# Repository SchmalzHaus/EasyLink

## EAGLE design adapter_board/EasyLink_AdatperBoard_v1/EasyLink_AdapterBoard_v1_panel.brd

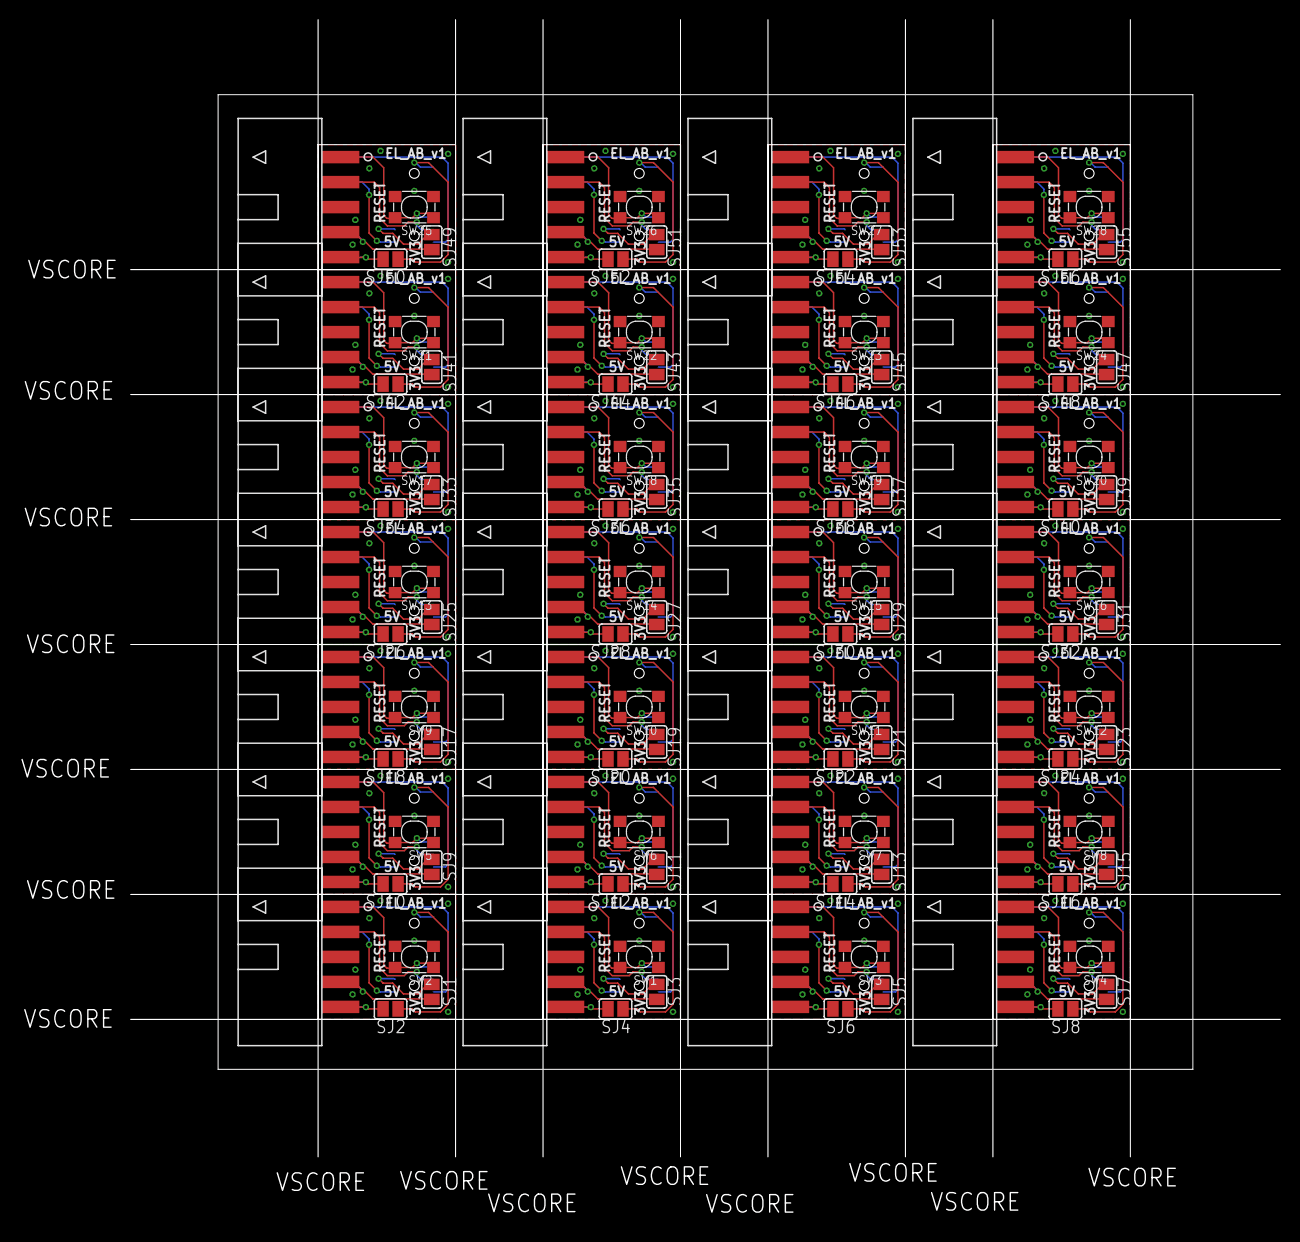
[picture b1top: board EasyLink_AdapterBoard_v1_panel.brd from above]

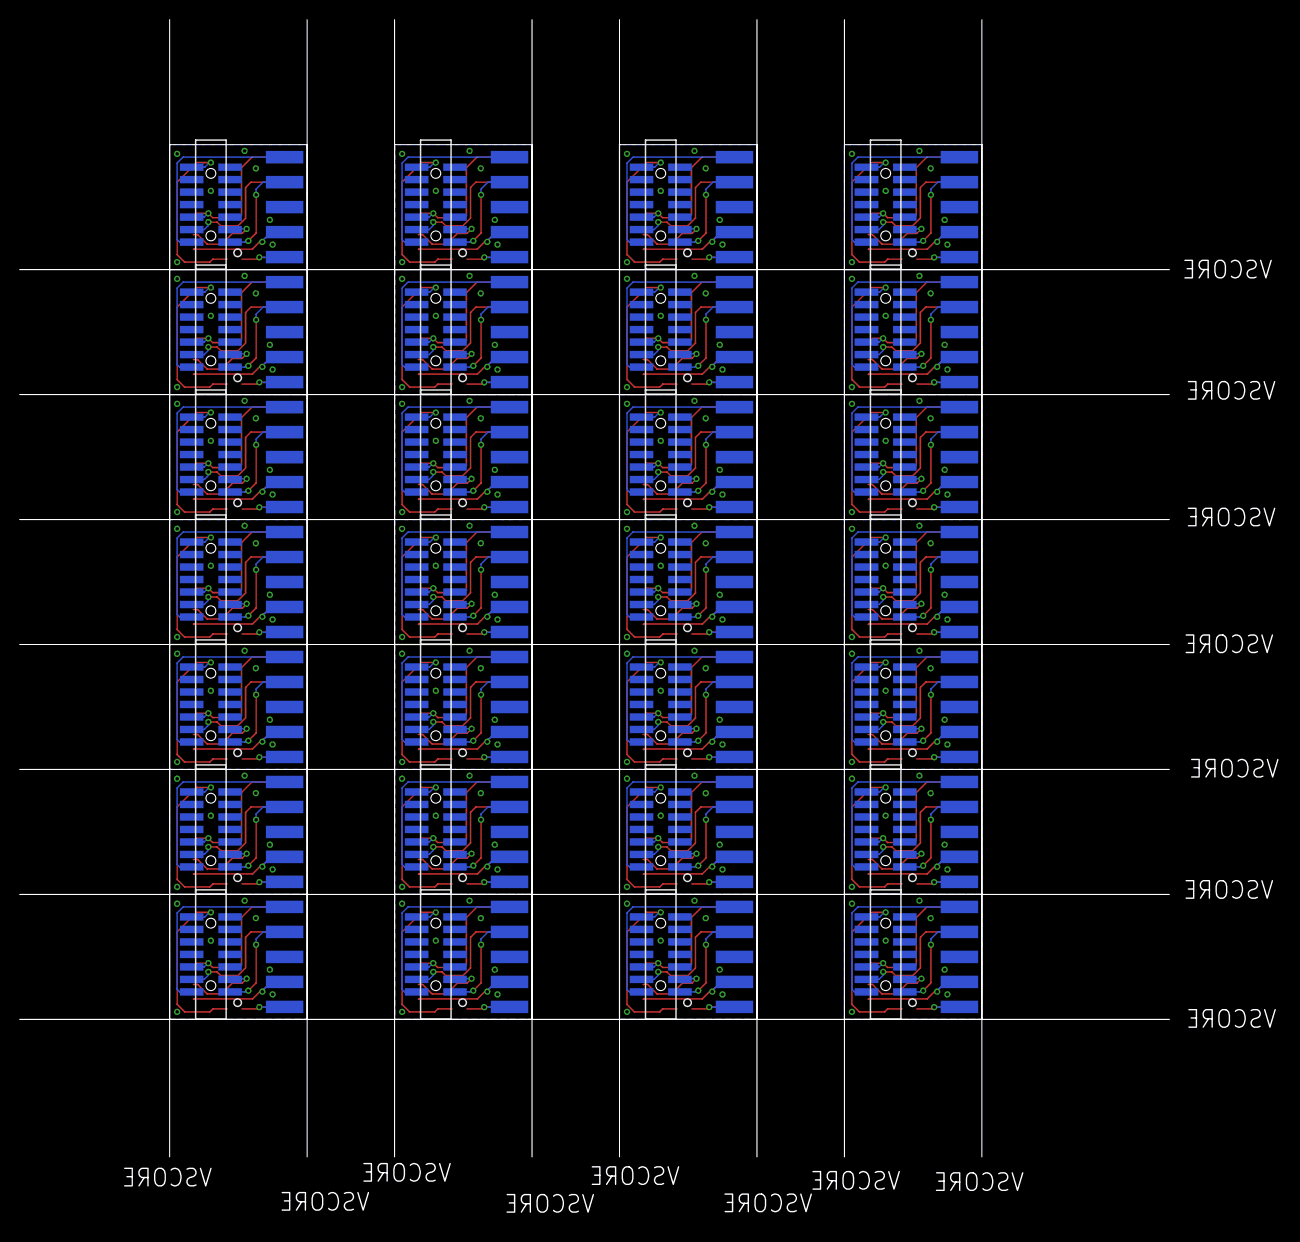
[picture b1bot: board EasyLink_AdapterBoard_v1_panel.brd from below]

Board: 4 copper layers, 116.8 x 115.6 mm, 140 parts (28 on the bottom side), 252 nets.

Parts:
SJ1, SJ2, SJ3, SJ4, SJ5, SJ6, SJ7, SJ8, SJ9, SJ10, SJ11, SJ12, SJ13, SJ14, SJ15, SJ16, SJ17, SJ18, SJ19, SJ20, SJ21, SJ22, SJ23, SJ24, SJ25, SJ26, SJ27, SJ28, SJ29, SJ30, SJ31, SJ32, SJ33, SJ34, SJ35, SJ36, SJ37, SJ38, SJ39, SJ40, SJ41, SJ42, SJ43, SJ44, SJ45, SJ46, SJ47, SJ48, SJ49, SJ50, SJ51, SJ52, SJ53, SJ54, SJ55, SJ56: SJ
SW1, SW2, SW3, SW4, SW5, SW6, SW7, SW8, SW9, SW10, SW11, SW12, SW13, SW14, SW15, SW16, SW17, SW18, SW19, SW20, SW21, SW22, SW23, SW24, SW25, SW26, SW27, SW28: DHT-4235A; SW4-SMD-4.2X3.2X2.5MM
U$1, U$3, U$5, U$7, U$9, U$11, U$13, U$15, U$17, U$19, U$21, U$23, U$25, U$27, U$29, U$31, U$33, U$35, U$37, U$39, U$41, U$43, U$45, U$47, U$49, U$51, U$53, U$55: 2X7_DEBUG_HEADFER; 20021121_2X7_SMT_MALE
U$2, U$4, U$6, U$8, U$10, U$12, U$14, U$16, U$18, U$20, U$22, U$24, U$26, U$28, U$30, U$32, U$34, U$36, U$38, U$40, U$42, U$44, U$46, U$48, U$50, U$52, U$54, U$56: SFH11-2X5STRAIGHT; SFH11-2X5-STRAIGHT

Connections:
GND: SW2.3, SW2.4, U$1.P$5, U$1.P$7, U$1.P$8, U$2.P5, U$2.P6
GND1: SW1.3, SW1.4, U$3.P$5, U$3.P$7, U$3.P$8, U$4.P5, U$4.P6
GND2: SW3.3, SW3.4, U$5.P$5, U$5.P$7, U$5.P$8, U$6.P5, U$6.P6
GND3: SW4.3, SW4.4, U$7.P$5, U$7.P$7, U$7.P$8, U$8.P5, U$8.P6
GND4: SW5.3, SW5.4, U$9.P$5, U$9.P$7, U$9.P$8, U$10.P5, U$10.P6
GND5: SW6.3, SW6.4, U$11.P$5, U$11.P$7, U$11.P$8, U$12.P5, U$12.P6
GND6: SW7.3, SW7.4, U$13.P$5, U$13.P$7, U$13.P$8, U$14.P5, U$14.P6
GND7: SW8.3, SW8.4, U$15.P$5, U$15.P$7, U$15.P$8, U$16.P5, U$16.P6
GND8: SW9.3, SW9.4, U$17.P$5, U$17.P$7, U$17.P$8, U$18.P5, U$18.P6
GND9: SW10.3, SW10.4, U$19.P$5, U$19.P$7, U$19.P$8, U$20.P5, U$20.P6
GND10: SW11.3, SW11.4, U$21.P$5, U$21.P$7, U$21.P$8, U$22.P5, U$22.P6
GND11: SW12.3, SW12.4, U$23.P$5, U$23.P$7, U$23.P$8, U$24.P5, U$24.P6
GND12: SW13.3, SW13.4, U$25.P$5, U$25.P$7, U$25.P$8, U$26.P5, U$26.P6
GND13: SW14.3, SW14.4, U$27.P$5, U$27.P$7, U$27.P$8, U$28.P5, U$28.P6
GND14: SW15.3, SW15.4, U$29.P$5, U$29.P$7, U$29.P$8, U$30.P5, U$30.P6
GND15: SW16.3, SW16.4, U$31.P$5, U$31.P$7, U$31.P$8, U$32.P5, U$32.P6
GND16: SW17.3, SW17.4, U$33.P$5, U$33.P$7, U$33.P$8, U$34.P5, U$34.P6
GND17: SW18.3, SW18.4, U$35.P$5, U$35.P$7, U$35.P$8, U$36.P5, U$36.P6
GND18: SW19.3, SW19.4, U$37.P$5, U$37.P$7, U$37.P$8, U$38.P5, U$38.P6
GND19: SW20.3, SW20.4, U$39.P$5, U$39.P$7, U$39.P$8, U$40.P5, U$40.P6
GND20: SW21.3, SW21.4, U$41.P$5, U$41.P$7, U$41.P$8, U$42.P5, U$42.P6
GND21: SW22.3, SW22.4, U$43.P$5, U$43.P$7, U$43.P$8, U$44.P5, U$44.P6
GND22: SW23.3, SW23.4, U$45.P$5, U$45.P$7, U$45.P$8, U$46.P5, U$46.P6
GND23: SW24.3, SW24.4, U$47.P$5, U$47.P$7, U$47.P$8, U$48.P5, U$48.P6
GND24: SW25.3, SW25.4, U$49.P$5, U$49.P$7, U$49.P$8, U$50.P5, U$50.P6
GND25: SW26.3, SW26.4, U$51.P$5, U$51.P$7, U$51.P$8, U$52.P5, U$52.P6
GND26: SW27.3, SW27.4, U$53.P$5, U$53.P$7, U$53.P$8, U$54.P5, U$54.P6
GND27: SW28.3, SW28.4, U$55.P$5, U$55.P$7, U$55.P$8, U$56.P5, U$56.P6
unnamed: U$1.P$1, U$2.P4
unnamed: U$1.P$2, U$2.P2
unnamed: SJ1.2, U$2.P7, U$2.P8
unnamed: U$1.P$4, U$2.P3
unnamed: SJ2.1, U$1.P$14
unnamed: U$3.P$1, U$4.P4
unnamed: SJ2.2, U$2.P9, U$2.P10
unnamed: SJ1.1, U$1.P$3
unnamed: U$3.P$2, U$4.P2
unnamed: SJ3.2, U$4.P7, U$4.P8
unnamed: U$3.P$4, U$4.P3
unnamed: SJ4.2, U$4.P9, U$4.P10
unnamed: SJ4.1, U$3.P$14
unnamed: SJ3.1, U$3.P$3
unnamed: U$5.P$1, U$6.P4
unnamed: U$5.P$2, U$6.P2
unnamed: SJ5.2, U$6.P7, U$6.P8
unnamed: U$5.P$4, U$6.P3
unnamed: SJ6.2, U$6.P9, U$6.P10
unnamed: SJ6.1, U$5.P$14
unnamed: SJ5.1, U$5.P$3
unnamed: U$7.P$1, U$8.P4
unnamed: U$7.P$2, U$8.P2
unnamed: SJ7.2, U$8.P7, U$8.P8
unnamed: U$7.P$4, U$8.P3
unnamed: SJ8.2, U$8.P9, U$8.P10
unnamed: SJ8.1, U$7.P$14
unnamed: SJ7.1, U$7.P$3
unnamed: U$9.P$1, U$10.P4
unnamed: U$9.P$2, U$10.P2
unnamed: SJ9.2, U$10.P7, U$10.P8
unnamed: U$9.P$4, U$10.P3
unnamed: SJ10.2, U$10.P9, U$10.P10
unnamed: SJ10.1, U$9.P$14
unnamed: SJ9.1, U$9.P$3
unnamed: U$11.P$1, U$12.P4
unnamed: U$11.P$2, U$12.P2
unnamed: SJ11.2, U$12.P7, U$12.P8
unnamed: U$11.P$4, U$12.P3
unnamed: SJ12.2, U$12.P9, U$12.P10
unnamed: SJ12.1, U$11.P$14
unnamed: SJ11.1, U$11.P$3
unnamed: U$13.P$1, U$14.P4
unnamed: U$13.P$2, U$14.P2
unnamed: SJ13.2, U$14.P7, U$14.P8
unnamed: U$13.P$4, U$14.P3
unnamed: SJ14.2, U$14.P9, U$14.P10
unnamed: SJ14.1, U$13.P$14
unnamed: SJ13.1, U$13.P$3
unnamed: U$15.P$1, U$16.P4
unnamed: U$15.P$2, U$16.P2
unnamed: SJ15.2, U$16.P7, U$16.P8
unnamed: U$15.P$4, U$16.P3
unnamed: SJ16.2, U$16.P9, U$16.P10
unnamed: SJ16.1, U$15.P$14
unnamed: SJ15.1, U$15.P$3
unnamed: U$17.P$1, U$18.P4
unnamed: U$17.P$2, U$18.P2
unnamed: SJ17.2, U$18.P7, U$18.P8
unnamed: U$17.P$4, U$18.P3
unnamed: SJ18.2, U$18.P9, U$18.P10
unnamed: SJ18.1, U$17.P$14
unnamed: SJ17.1, U$17.P$3
unnamed: U$19.P$1, U$20.P4
unnamed: U$19.P$2, U$20.P2
unnamed: SJ19.2, U$20.P7, U$20.P8
unnamed: U$19.P$4, U$20.P3
unnamed: SJ20.2, U$20.P9, U$20.P10
unnamed: SJ20.1, U$19.P$14
unnamed: SJ19.1, U$19.P$3
unnamed: U$21.P$1, U$22.P4
unnamed: U$21.P$2, U$22.P2
unnamed: SJ21.2, U$22.P7, U$22.P8
unnamed: U$21.P$4, U$22.P3
unnamed: SJ22.2, U$22.P9, U$22.P10
unnamed: SJ22.1, U$21.P$14
unnamed: SJ21.1, U$21.P$3
unnamed: U$23.P$1, U$24.P4
unnamed: U$23.P$2, U$24.P2
unnamed: SJ23.2, U$24.P7, U$24.P8
unnamed: U$23.P$4, U$24.P3
unnamed: SJ24.2, U$24.P9, U$24.P10
unnamed: SJ24.1, U$23.P$14
unnamed: SJ23.1, U$23.P$3
unnamed: U$25.P$1, U$26.P4
unnamed: U$25.P$2, U$26.P2
unnamed: SJ25.2, U$26.P7, U$26.P8
unnamed: U$25.P$4, U$26.P3
unnamed: SJ26.2, U$26.P9, U$26.P10
unnamed: SJ26.1, U$25.P$14
unnamed: SJ25.1, U$25.P$3
unnamed: U$27.P$1, U$28.P4
unnamed: U$27.P$2, U$28.P2
unnamed: SJ27.2, U$28.P7, U$28.P8
unnamed: U$27.P$4, U$28.P3
unnamed: SJ28.2, U$28.P9, U$28.P10
unnamed: SJ28.1, U$27.P$14
unnamed: SJ27.1, U$27.P$3
unnamed: U$29.P$1, U$30.P4
unnamed: U$29.P$2, U$30.P2
unnamed: SJ29.2, U$30.P7, U$30.P8
unnamed: U$29.P$4, U$30.P3
unnamed: SJ30.2, U$30.P9, U$30.P10
unnamed: SJ30.1, U$29.P$14
unnamed: SJ29.1, U$29.P$3
unnamed: U$31.P$1, U$32.P4
unnamed: U$31.P$2, U$32.P2
unnamed: SJ31.2, U$32.P7, U$32.P8
unnamed: U$31.P$4, U$32.P3
unnamed: SJ32.2, U$32.P9, U$32.P10
unnamed: SJ32.1, U$31.P$14
unnamed: SJ31.1, U$31.P$3
unnamed: U$33.P$1, U$34.P4
unnamed: U$33.P$2, U$34.P2
unnamed: SJ33.2, U$34.P7, U$34.P8
unnamed: U$33.P$4, U$34.P3
unnamed: SJ34.2, U$34.P9, U$34.P10
unnamed: SJ34.1, U$33.P$14
unnamed: SJ33.1, U$33.P$3
unnamed: U$35.P$1, U$36.P4
unnamed: U$35.P$2, U$36.P2
unnamed: SJ35.2, U$36.P7, U$36.P8
unnamed: U$35.P$4, U$36.P3
unnamed: SJ36.2, U$36.P9, U$36.P10
unnamed: SJ36.1, U$35.P$14
unnamed: SJ35.1, U$35.P$3
unnamed: U$37.P$1, U$38.P4
unnamed: U$37.P$2, U$38.P2
unnamed: SJ37.2, U$38.P7, U$38.P8
unnamed: U$37.P$4, U$38.P3
unnamed: SJ38.2, U$38.P9, U$38.P10
unnamed: SJ38.1, U$37.P$14
unnamed: SJ37.1, U$37.P$3
unnamed: U$39.P$1, U$40.P4
unnamed: U$39.P$2, U$40.P2
unnamed: SJ39.2, U$40.P7, U$40.P8
unnamed: U$39.P$4, U$40.P3
unnamed: SJ40.2, U$40.P9, U$40.P10
unnamed: SJ40.1, U$39.P$14
unnamed: SJ39.1, U$39.P$3
unnamed: U$41.P$1, U$42.P4
unnamed: U$41.P$2, U$42.P2
unnamed: SJ41.2, U$42.P7, U$42.P8
unnamed: U$41.P$4, U$42.P3
unnamed: SJ42.2, U$42.P9, U$42.P10
unnamed: SJ42.1, U$41.P$14
unnamed: SJ41.1, U$41.P$3
unnamed: U$43.P$1, U$44.P4
unnamed: U$43.P$2, U$44.P2
unnamed: SJ43.2, U$44.P7, U$44.P8
unnamed: U$43.P$4, U$44.P3
unnamed: SJ44.2, U$44.P9, U$44.P10
unnamed: SJ44.1, U$43.P$14
unnamed: SJ43.1, U$43.P$3
unnamed: U$45.P$1, U$46.P4
unnamed: U$45.P$2, U$46.P2
unnamed: SJ45.2, U$46.P7, U$46.P8
unnamed: U$45.P$4, U$46.P3
unnamed: SJ46.2, U$46.P9, U$46.P10
unnamed: SJ46.1, U$45.P$14
unnamed: SJ45.1, U$45.P$3
unnamed: U$47.P$1, U$48.P4
unnamed: U$47.P$2, U$48.P2
unnamed: SJ47.2, U$48.P7, U$48.P8
unnamed: U$47.P$4, U$48.P3
unnamed: SJ48.2, U$48.P9, U$48.P10
unnamed: SJ48.1, U$47.P$14
unnamed: SJ47.1, U$47.P$3
unnamed: U$49.P$1, U$50.P4
unnamed: U$49.P$2, U$50.P2
unnamed: SJ49.2, U$50.P7, U$50.P8
unnamed: U$49.P$4, U$50.P3
unnamed: SJ50.2, U$50.P9, U$50.P10
unnamed: SJ50.1, U$49.P$14
unnamed: SJ49.1, U$49.P$3
unnamed: U$51.P$1, U$52.P4
unnamed: U$51.P$2, U$52.P2
unnamed: SJ51.2, U$52.P7, U$52.P8
unnamed: U$51.P$4, U$52.P3
unnamed: SJ52.2, U$52.P9, U$52.P10
unnamed: SJ52.1, U$51.P$14
unnamed: SJ51.1, U$51.P$3
unnamed: U$53.P$1, U$54.P4
unnamed: U$53.P$2, U$54.P2
unnamed: SJ53.2, U$54.P7, U$54.P8
unnamed: U$53.P$4, U$54.P3
unnamed: SJ54.2, U$54.P9, U$54.P10
unnamed: SJ54.1, U$53.P$14
unnamed: SJ53.1, U$53.P$3
unnamed: U$55.P$1, U$56.P4
unnamed: U$55.P$2, U$56.P2
unnamed: SJ55.2, U$56.P7, U$56.P8
unnamed: U$55.P$4, U$56.P3
unnamed: SJ56.2, U$56.P9, U$56.P10
unnamed: SJ56.1, U$55.P$14
unnamed: SJ55.1, U$55.P$3
PRG_SW: SW2.1, SW2.2, U$1.P$6, U$2.P1
PRG_SW1: SW1.1, SW1.2, U$3.P$6, U$4.P1
PRG_SW2: SW3.1, SW3.2, U$5.P$6, U$6.P1
PRG_SW3: SW4.1, SW4.2, U$7.P$6, U$8.P1
PRG_SW4: SW5.1, SW5.2, U$9.P$6, U$10.P1
PRG_SW5: SW6.1, SW6.2, U$11.P$6, U$12.P1
PRG_SW6: SW7.1, SW7.2, U$13.P$6, U$14.P1
PRG_SW7: SW8.1, SW8.2, U$15.P$6, U$16.P1
PRG_SW8: SW9.1, SW9.2, U$17.P$6, U$18.P1
PRG_SW9: SW10.1, SW10.2, U$19.P$6, U$20.P1
PRG_SW10: SW11.1, SW11.2, U$21.P$6, U$22.P1
PRG_SW11: SW12.1, SW12.2, U$23.P$6, U$24.P1
PRG_SW12: SW13.1, SW13.2, U$25.P$6, U$26.P1
PRG_SW13: SW14.1, SW14.2, U$27.P$6, U$28.P1
PRG_SW14: SW15.1, SW15.2, U$29.P$6, U$30.P1
PRG_SW15: SW16.1, SW16.2, U$31.P$6, U$32.P1
PRG_SW16: SW17.1, SW17.2, U$33.P$6, U$34.P1
PRG_SW17: SW18.1, SW18.2, U$35.P$6, U$36.P1
PRG_SW18: SW19.1, SW19.2, U$37.P$6, U$38.P1
PRG_SW19: SW20.1, SW20.2, U$39.P$6, U$40.P1
PRG_SW20: SW21.1, SW21.2, U$41.P$6, U$42.P1
PRG_SW21: SW22.1, SW22.2, U$43.P$6, U$44.P1
PRG_SW22: SW23.1, SW23.2, U$45.P$6, U$46.P1
PRG_SW23: SW24.1, SW24.2, U$47.P$6, U$48.P1
PRG_SW24: SW25.1, SW25.2, U$49.P$6, U$50.P1
PRG_SW25: SW26.1, SW26.2, U$51.P$6, U$52.P1
PRG_SW26: SW27.1, SW27.2, U$53.P$6, U$54.P1
PRG_SW27: SW28.1, SW28.2, U$55.P$6, U$56.P1

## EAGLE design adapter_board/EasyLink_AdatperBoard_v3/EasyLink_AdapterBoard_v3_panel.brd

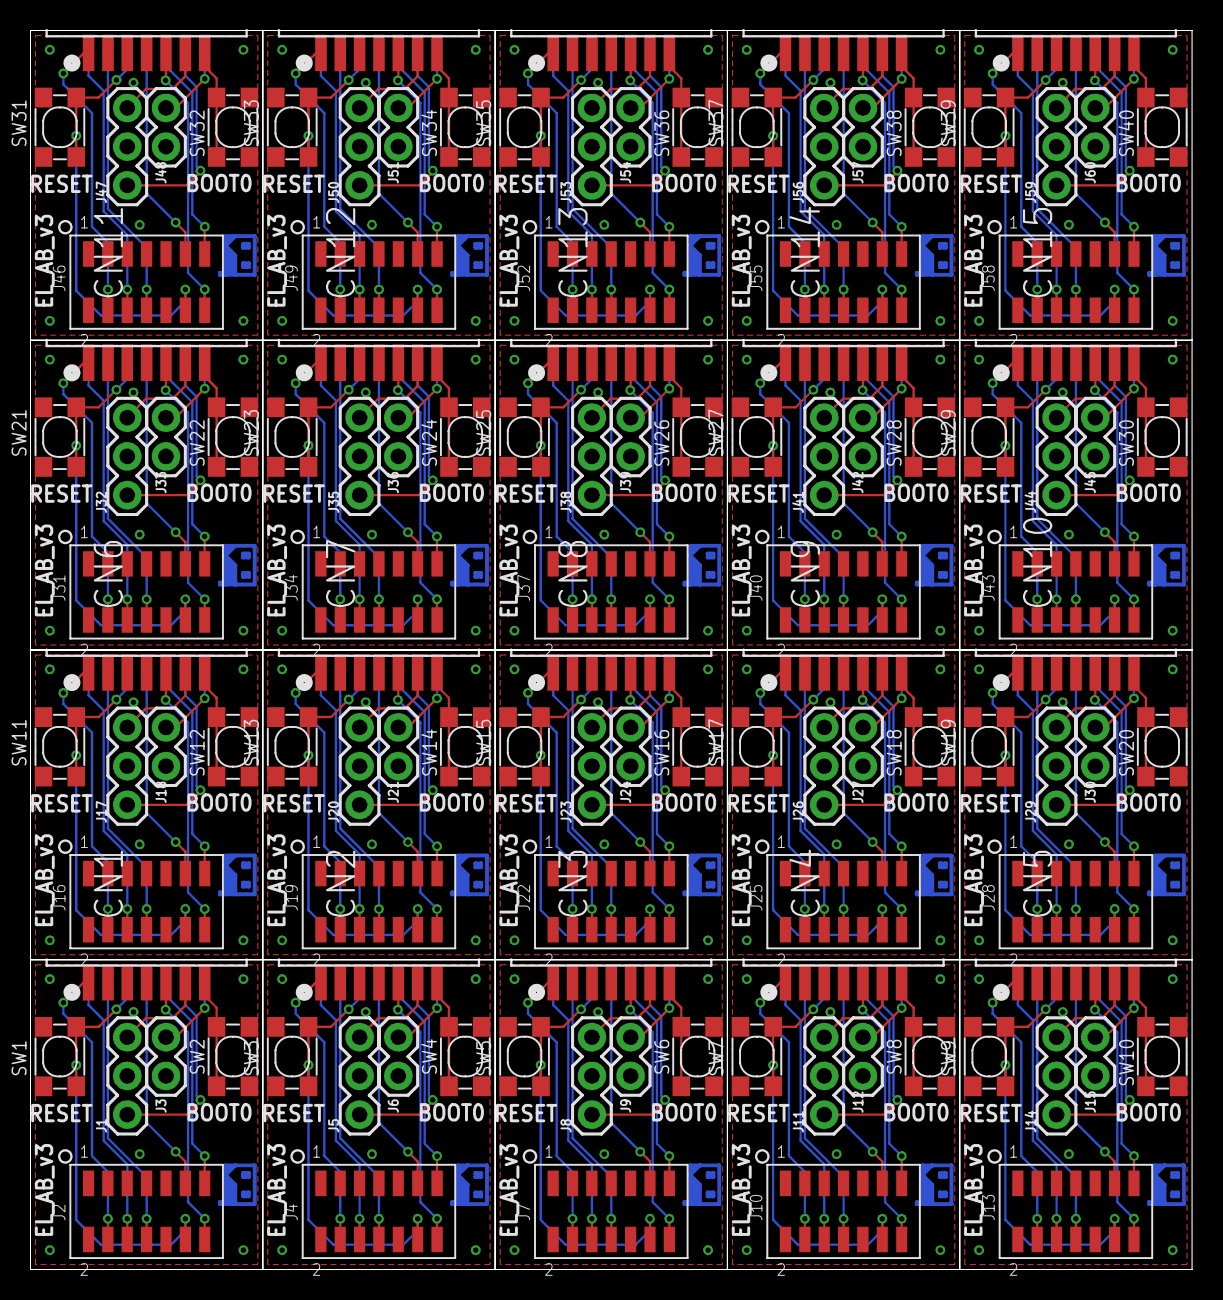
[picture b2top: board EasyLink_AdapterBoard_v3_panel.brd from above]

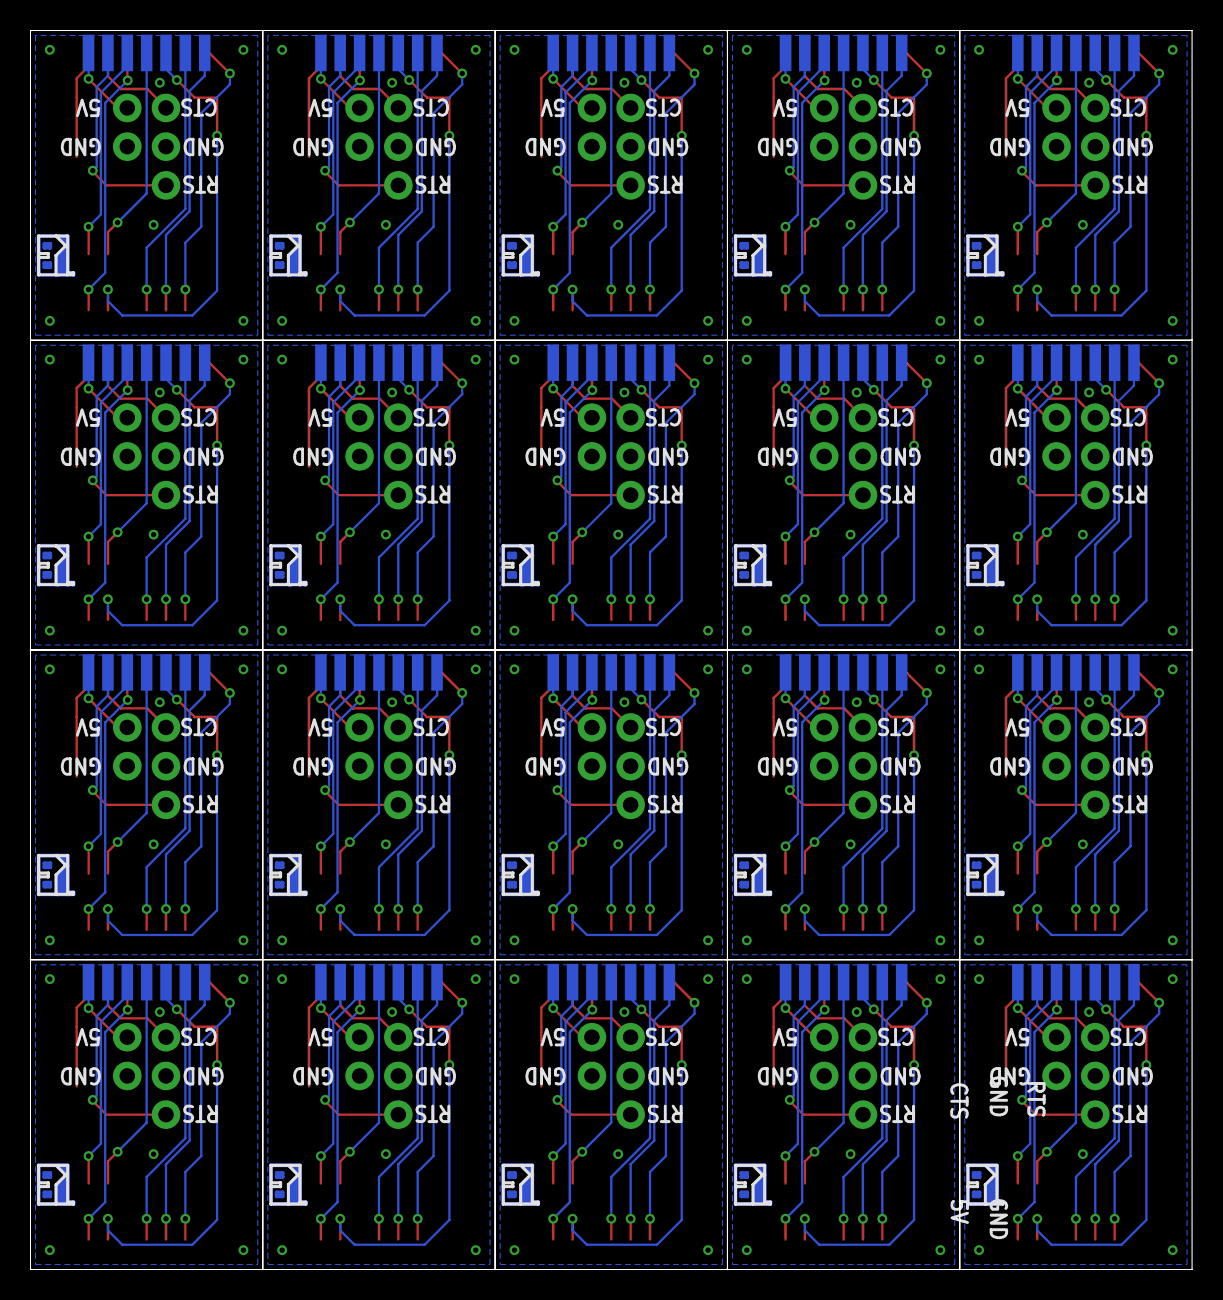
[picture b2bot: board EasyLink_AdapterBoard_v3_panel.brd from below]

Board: 2 copper layers, 76.2 x 81.3 mm, 140 parts (20 on the bottom side), 240 nets.

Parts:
CN1, CN2, CN3, CN4, CN5, CN6, CN7, CN8, CN9, CN10, CN11, CN12, CN13, CN14, CN15, CN16, CN17, CN18, CN19, CN20: 2X7_DEBUG_HEADFEREDGE; 2X7_MALE_BOARD_STRADDLE
J1, J5, J8, J11, J14, J17, J20, J23, J26, J29, J32, J35, J38, J41, J44, J47, J50, J53, J56, J59: 1X03
J2, J4, J7, J10, J13, J16, J19, J22, J25, J28, J31, J34, J37, J40, J43, J46, J49, J52, J55, J58: FLE-107-01-XX-DV
J3, J6, J9, J12, J15, J18, J21, J24, J27, J30, J33, J36, J39, J42, J45, J48, J51, J54, J57, J60: 1X02
SW1, SW2, SW3, SW4, SW5, SW6, SW7, SW8, SW9, SW10, SW11, SW12, SW13, SW14, SW15, SW16, SW17, SW18, SW19, SW20, SW21, SW22, SW23, SW24, SW25, SW26, SW27, SW28, SW29, SW30, SW31, SW32, SW33, SW34, SW35, SW36, SW37, SW38, SW39, SW40: DHT-4235A; SW4-SMD-4.2X3.2X2.5MM
U$1, U$2, U$3, U$4, U$5, U$6, U$7, U$8, U$9, U$10, U$11, U$12, U$13, U$14, U$15, U$16, U$17, U$18, U$19, U$20: SCHMALZHAUSSCHMALZHAUS_SMALL; SCHMALZHAUS_SMALL

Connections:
5V: CN1.P$14, J3.1
5V1: CN2.P$14, J6.1
5V2: CN3.P$14, J9.1
5V3: CN4.P$14, J12.1
5V4: CN5.P$14, J15.1
5V5: CN6.P$14, J18.1
5V6: CN7.P$14, J21.1
5V7: CN8.P$14, J24.1
5V8: CN9.P$14, J27.1
5V9: CN10.P$14, J30.1
5V10: CN11.P$14, J33.1
5V11: CN12.P$14, J36.1
5V12: CN13.P$14, J39.1
5V13: CN14.P$14, J42.1
5V14: CN15.P$14, J45.1
5V15: CN16.P$14, J48.1
5V16: CN17.P$14, J51.1
5V17: CN18.P$14, J54.1
5V18: CN19.P$14, J57.1
5V19: CN20.P$14, J60.1
BOOT0: CN1.P$13, SW2.1, SW2.2
BOOT1: CN2.P$13, SW4.1, SW4.2
BOOT2: CN3.P$13, SW6.1, SW6.2
BOOT3: CN4.P$13, SW8.1, SW8.2
BOOT4: CN5.P$13, SW10.1, SW10.2
BOOT5: CN6.P$13, SW12.1, SW12.2
BOOT6: CN7.P$13, SW14.1, SW14.2
BOOT7: CN8.P$13, SW16.1, SW16.2
BOOT8: CN9.P$13, SW18.1, SW18.2
BOOT9: CN10.P$13, SW20.1, SW20.2
BOOT10: CN11.P$13, SW22.1, SW22.2
BOOT11: CN12.P$13, SW24.1, SW24.2
BOOT12: CN13.P$13, SW26.1, SW26.2
BOOT13: CN14.P$13, SW28.1, SW28.2
BOOT14: CN15.P$13, SW30.1, SW30.2
BOOT15: CN16.P$13, SW32.1, SW32.2
BOOT16: CN17.P$13, SW34.1, SW34.2
BOOT17: CN18.P$13, SW36.1, SW36.2
BOOT18: CN19.P$13, SW38.1, SW38.2
BOOT19: CN20.P$13, SW40.1, SW40.2
CTS: CN1.P$11, J1.3
CTS1: CN2.P$11, J5.3
CTS2: CN3.P$11, J8.3
CTS3: CN4.P$11, J11.3
CTS4: CN5.P$11, J14.3
CTS5: CN6.P$11, J17.3
CTS6: CN7.P$11, J20.3
CTS7: CN8.P$11, J23.3
CTS8: CN9.P$11, J26.3
CTS9: CN10.P$11, J29.3
CTS10: CN11.P$11, J32.3
CTS11: CN12.P$11, J35.3
CTS12: CN13.P$11, J38.3
CTS13: CN14.P$11, J41.3
CTS14: CN15.P$11, J44.3
CTS15: CN16.P$11, J47.3
CTS16: CN17.P$11, J50.3
CTS17: CN18.P$11, J53.3
CTS18: CN19.P$11, J56.3
CTS19: CN20.P$11, J59.3
GND: CN1.P$5, CN1.P$7, J1.2, J2.5, J2.7, J3.2, SW1.3, SW1.4, SW2.3, SW2.4
GND1: CN2.P$5, CN2.P$7, J4.5, J4.7, J5.2, J6.2, SW3.3, SW3.4, SW4.3, SW4.4
GND2: CN3.P$5, CN3.P$7, J7.5, J7.7, J8.2, J9.2, SW5.3, SW5.4, SW6.3, SW6.4
GND3: CN4.P$5, CN4.P$7, J10.5, J10.7, J11.2, J12.2, SW7.3, SW7.4, SW8.3, SW8.4
GND4: CN5.P$5, CN5.P$7, J13.5, J13.7, J14.2, J15.2, SW9.3, SW9.4, SW10.3, SW10.4
GND5: CN6.P$5, CN6.P$7, J16.5, J16.7, J17.2, J18.2, SW11.3, SW11.4, SW12.3, SW12.4
GND6: CN7.P$5, CN7.P$7, J19.5, J19.7, J20.2, J21.2, SW13.3, SW13.4, SW14.3, SW14.4
GND7: CN8.P$5, CN8.P$7, J22.5, J22.7, J23.2, J24.2, SW15.3, SW15.4, SW16.3, SW16.4
GND8: CN9.P$5, CN9.P$7, J25.5, J25.7, J26.2, J27.2, SW17.3, SW17.4, SW18.3, SW18.4
GND9: CN10.P$5, CN10.P$7, J28.5, J28.7, J29.2, J30.2, SW19.3, SW19.4, SW20.3, SW20.4
GND10: CN11.P$5, CN11.P$7, J31.5, J31.7, J32.2, J33.2, SW21.3, SW21.4, SW22.3, SW22.4
GND11: CN12.P$5, CN12.P$7, J34.5, J34.7, J35.2, J36.2, SW23.3, SW23.4, SW24.3, SW24.4
GND12: CN13.P$5, CN13.P$7, J37.5, J37.7, J38.2, J39.2, SW25.3, SW25.4, SW26.3, SW26.4
GND13: CN14.P$5, CN14.P$7, J40.5, J40.7, J41.2, J42.2, SW27.3, SW27.4, SW28.3, SW28.4
GND14: CN15.P$5, CN15.P$7, J43.5, J43.7, J44.2, J45.2, SW29.3, SW29.4, SW30.3, SW30.4
GND15: CN16.P$5, CN16.P$7, J46.5, J46.7, J47.2, J48.2, SW31.3, SW31.4, SW32.3, SW32.4
GND16: CN17.P$5, CN17.P$7, J49.5, J49.7, J50.2, J51.2, SW33.3, SW33.4, SW34.3, SW34.4
GND17: CN18.P$5, CN18.P$7, J52.5, J52.7, J53.2, J54.2, SW35.3, SW35.4, SW36.3, SW36.4
GND18: CN19.P$5, CN19.P$7, J55.5, J55.7, J56.2, J57.2, SW37.3, SW37.4, SW38.3, SW38.4
GND19: CN20.P$5, CN20.P$7, J58.5, J58.7, J59.2, J60.2, SW39.3, SW39.4, SW40.3, SW40.4
NRST: CN1.P$6, J2.12, SW1.1, SW1.2
NRST1: CN2.P$6, J4.12, SW3.1, SW3.2
NRST2: CN3.P$6, J7.12, SW5.1, SW5.2
NRST3: CN4.P$6, J10.12, SW7.1, SW7.2
NRST4: CN5.P$6, J13.12, SW9.1, SW9.2
NRST5: CN6.P$6, J16.12, SW11.1, SW11.2
NRST6: CN7.P$6, J19.12, SW13.1, SW13.2
NRST7: CN8.P$6, J22.12, SW15.1, SW15.2
NRST8: CN9.P$6, J25.12, SW17.1, SW17.2
NRST9: CN10.P$6, J28.12, SW19.1, SW19.2
NRST10: CN11.P$6, J31.12, SW21.1, SW21.2
NRST11: CN12.P$6, J34.12, SW23.1, SW23.2
NRST12: CN13.P$6, J37.12, SW25.1, SW25.2
NRST13: CN14.P$6, J40.12, SW27.1, SW27.2
NRST14: CN15.P$6, J43.12, SW29.1, SW29.2
NRST15: CN16.P$6, J46.12, SW31.1, SW31.2
NRST16: CN17.P$6, J49.12, SW33.1, SW33.2
NRST17: CN18.P$6, J52.12, SW35.1, SW35.2
NRST18: CN19.P$6, J55.12, SW37.1, SW37.2
NRST19: CN20.P$6, J58.12, SW39.1, SW39.2
RTS: CN1.P$12, J1.1
RTS1: CN2.P$12, J5.1
RTS2: CN3.P$12, J8.1
RTS3: CN4.P$12, J11.1
RTS4: CN5.P$12, J14.1
RTS5: CN6.P$12, J17.1
RTS6: CN7.P$12, J20.1
RTS7: CN8.P$12, J23.1
RTS8: CN9.P$12, J26.1
RTS9: CN10.P$12, J29.1
RTS10: CN11.P$12, J32.1
RTS11: CN12.P$12, J35.1
RTS12: CN13.P$12, J38.1
RTS13: CN14.P$12, J41.1
RTS14: CN15.P$12, J44.1
RTS15: CN16.P$12, J47.1
RTS16: CN17.P$12, J50.1
RTS17: CN18.P$12, J53.1
RTS18: CN19.P$12, J56.1
RTS19: CN20.P$12, J59.1
SWCLK: CN1.P$2, J2.6
SWCLK1: CN2.P$2, J4.6
SWCLK2: CN3.P$2, J7.6
SWCLK3: CN4.P$2, J10.6
SWCLK4: CN5.P$2, J13.6
SWCLK5: CN6.P$2, J16.6
SWCLK6: CN7.P$2, J19.6
SWCLK7: CN8.P$2, J22.6
SWCLK8: CN9.P$2, J25.6
SWCLK9: CN10.P$2, J28.6
SWCLK10: CN11.P$2, J31.6
SWCLK11: CN12.P$2, J34.6
SWCLK12: CN13.P$2, J37.6
SWCLK13: CN14.P$2, J40.6
SWCLK14: CN15.P$2, J43.6
SWCLK15: CN16.P$2, J46.6
SWCLK16: CN17.P$2, J49.6
SWCLK17: CN18.P$2, J52.6
SWCLK18: CN19.P$2, J55.6
SWCLK19: CN20.P$2, J58.6
SWDIO: CN1.P$1, J2.4
SWDIO1: CN2.P$1, J4.4
SWDIO2: CN3.P$1, J7.4
SWDIO3: CN4.P$1, J10.4
SWDIO4: CN5.P$1, J13.4
SWDIO5: CN6.P$1, J16.4
SWDIO6: CN7.P$1, J19.4
SWDIO7: CN8.P$1, J22.4
SWDIO8: CN9.P$1, J25.4
SWDIO9: CN10.P$1, J28.4
SWDIO10: CN11.P$1, J31.4
SWDIO11: CN12.P$1, J34.4
SWDIO12: CN13.P$1, J37.4
SWDIO13: CN14.P$1, J40.4
SWDIO14: CN15.P$1, J43.4
SWDIO15: CN16.P$1, J46.4
SWDIO16: CN17.P$1, J49.4
SWDIO17: CN18.P$1, J52.4
SWDIO18: CN19.P$1, J55.4
SWDIO19: CN20.P$1, J58.4
SWO: CN1.P$4, J2.8
SWO1: CN2.P$4, J4.8
SWO2: CN3.P$4, J7.8
SWO3: CN4.P$4, J10.8
SWO4: CN5.P$4, J13.8
SWO5: CN6.P$4, J16.8
SWO6: CN7.P$4, J19.8
SWO7: CN8.P$4, J22.8
SWO8: CN9.P$4, J25.8
SWO9: CN10.P$4, J28.8
SWO10: CN11.P$4, J31.8
SWO11: CN12.P$4, J34.8
SWO12: CN13.P$4, J37.8
SWO13: CN14.P$4, J40.8
SWO14: CN15.P$4, J43.8
SWO15: CN16.P$4, J46.8
SWO16: CN17.P$4, J49.8
SWO17: CN18.P$4, J52.8
SWO18: CN19.P$4, J55.8
SWO19: CN20.P$4, J58.8
T_GND: CN1.P$8, J2.11
T_GND1: CN2.P$8, J4.11
T_GND2: CN3.P$8, J7.11
T_GND3: CN4.P$8, J10.11
T_GND4: CN5.P$8, J13.11
T_GND5: CN6.P$8, J16.11
T_GND6: CN7.P$8, J19.11
T_GND7: CN8.P$8, J22.11
T_GND8: CN9.P$8, J25.11
T_GND9: CN10.P$8, J28.11
T_GND10: CN11.P$8, J31.11
T_GND11: CN12.P$8, J34.11
T_GND12: CN13.P$8, J37.11
T_GND13: CN14.P$8, J40.11
T_GND14: CN15.P$8, J43.11
T_GND15: CN16.P$8, J46.11
T_GND16: CN17.P$8, J49.11
T_GND17: CN18.P$8, J52.11
T_GND18: CN19.P$8, J55.11
T_GND19: CN20.P$8, J58.11
VCP_RX_T_TX: CN1.P$9, J2.14
VCP_RX_T_TX1: CN2.P$9, J4.14
VCP_RX_T_TX2: CN3.P$9, J7.14
VCP_RX_T_TX3: CN4.P$9, J10.14
VCP_RX_T_TX4: CN5.P$9, J13.14
VCP_RX_T_TX5: CN6.P$9, J16.14
VCP_RX_T_TX6: CN7.P$9, J19.14
VCP_RX_T_TX7: CN8.P$9, J22.14
VCP_RX_T_TX8: CN9.P$9, J25.14
VCP_RX_T_TX9: CN10.P$9, J28.14
VCP_RX_T_TX10: CN11.P$9, J31.14
VCP_RX_T_TX11: CN12.P$9, J34.14
VCP_RX_T_TX12: CN13.P$9, J37.14
VCP_RX_T_TX13: CN14.P$9, J40.14
VCP_RX_T_TX14: CN15.P$9, J43.14
VCP_RX_T_TX15: CN16.P$9, J46.14
VCP_RX_T_TX16: CN17.P$9, J49.14
VCP_RX_T_TX17: CN18.P$9, J52.14
VCP_RX_T_TX18: CN19.P$9, J55.14
VCP_RX_T_TX19: CN20.P$9, J58.14
VCP_TX_T_RX: CN1.P$10, J2.13
VCP_TX_T_RX1: CN2.P$10, J4.13
VCP_TX_T_RX2: CN3.P$10, J7.13
VCP_TX_T_RX3: CN4.P$10, J10.13
VCP_TX_T_RX4: CN5.P$10, J13.13
VCP_TX_T_RX5: CN6.P$10, J16.13
VCP_TX_T_RX6: CN7.P$10, J19.13
VCP_TX_T_RX7: CN8.P$10, J22.13
VCP_TX_T_RX8: CN9.P$10, J25.13
VCP_TX_T_RX9: CN10.P$10, J28.13
VCP_TX_T_RX10: CN11.P$10, J31.13
VCP_TX_T_RX11: CN12.P$10, J34.13
VCP_TX_T_RX12: CN13.P$10, J37.13
VCP_TX_T_RX13: CN14.P$10, J40.13
VCP_TX_T_RX14: CN15.P$10, J43.13
VCP_TX_T_RX15: CN16.P$10, J46.13
VCP_TX_T_RX16: CN17.P$10, J49.13
VCP_TX_T_RX17: CN18.P$10, J52.13
VCP_TX_T_RX18: CN19.P$10, J55.13
VCP_TX_T_RX19: CN20.P$10, J58.13

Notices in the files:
parts and their libraries:
SparkFun-Connectors: Licensing: Creative Commons ShareAlike 4.0 International - https://creativecommons.org/licenses/by-sa/4.0
